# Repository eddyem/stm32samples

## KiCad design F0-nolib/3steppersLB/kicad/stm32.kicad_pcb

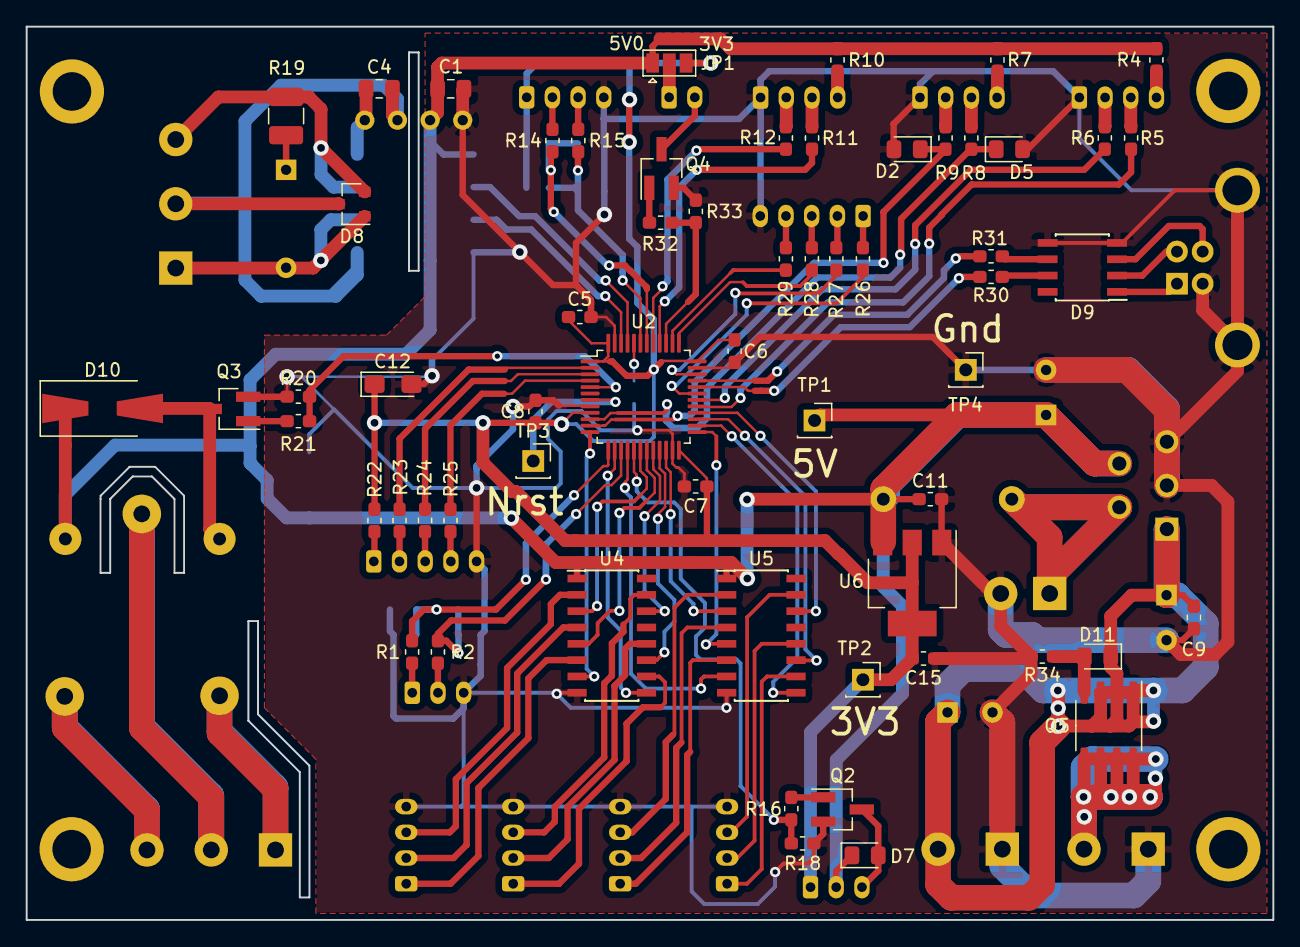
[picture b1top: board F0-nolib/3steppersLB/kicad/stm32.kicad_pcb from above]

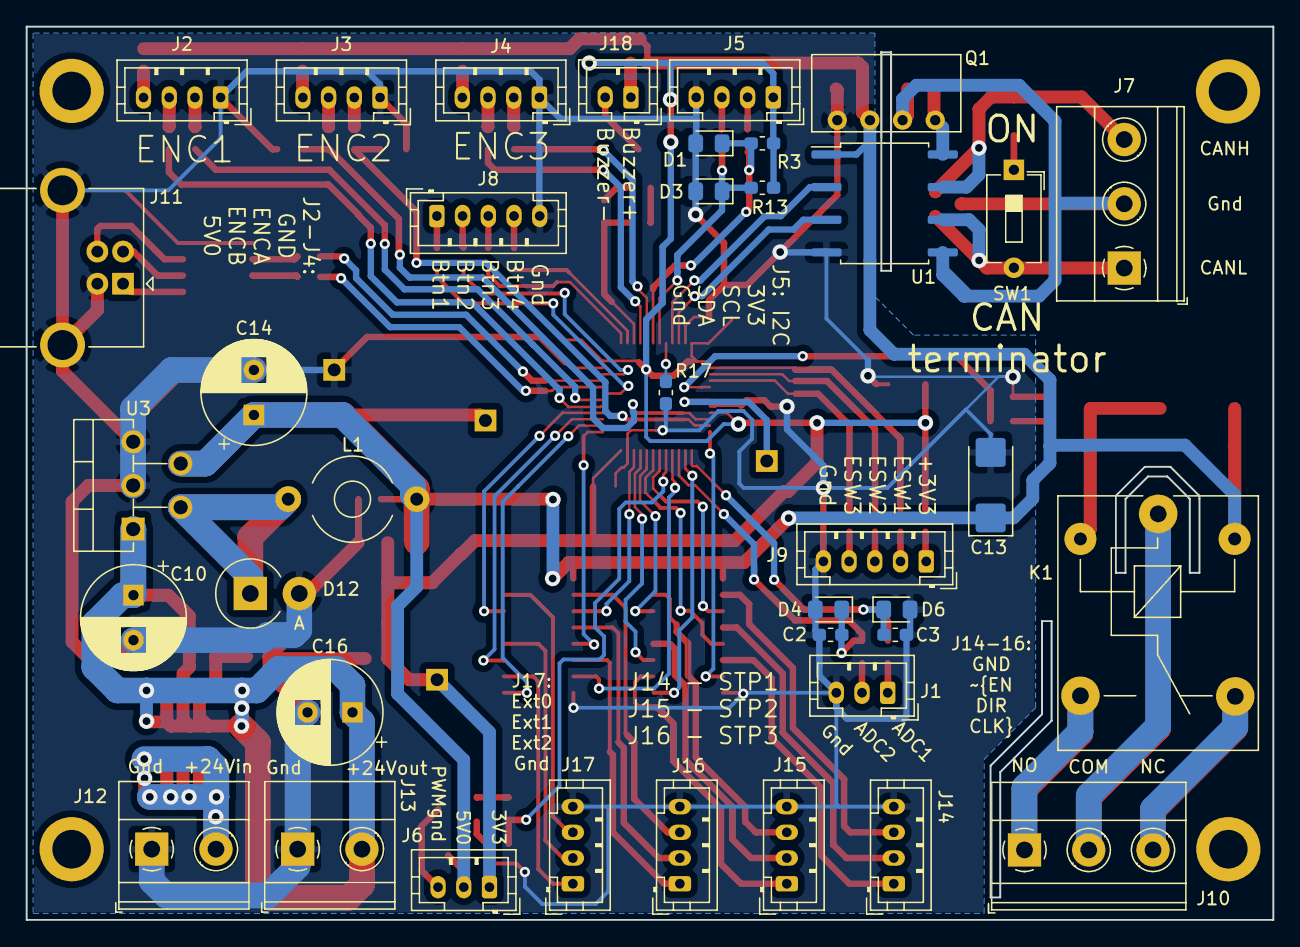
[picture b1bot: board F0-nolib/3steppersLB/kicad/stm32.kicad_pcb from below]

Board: 2 copper layers, 97.0 x 69.5 mm, 103 parts (38 on the bottom side), 98 nets.

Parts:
C1, C4: 1; C_0805_2012Metric_Pad1.15x1.40mm_HandSolder
C2, C3, C5, C6, C7, C8, C9, C11, C15: 0.1; C_0603_1608Metric_Pad1.05x0.95mm_HandSolder
C10, C14: 100u 16V; CP_Radial_D8.0mm_P3.50mm
C12: 47u 6V; CP_EIA-3216-18_Kemet-A_Pad1.58x1.35mm_HandSolder
C13: 47u 10V; CP_EIA-6032-28_Kemet-C_Pad2.25x2.35mm_HandSolder
C16: 100u 35V; CP_Radial_D8.0mm_P3.50mm
D1, D2, D3, D4, D5, D6: CESD3V3; D_0805_2012Metric_Pad1.15x1.40mm_HandSolder
D7: D; D_0805_2012Metric_Pad1.15x1.40mm_HandSolder
D8: PESD1CAN; SOT-23
D9: USB6B1; SOIC-8_3.9x4.9mm_P1.27mm
D10: SS14; D_SMA-SMB_Universal_Handsoldering
D11: MM3Z7V5; D_0805_2012Metric_Pad1.15x1.40mm_HandSolder
D12: 1N5822; D_DO-201_P3.81mm_Vertical_AnodeUp
J1, J6: 01x03; JST_PH_B3B-PH-K_1x03_P2.00mm_Vertical
J2, J3, J4, J5, J14, J15, J16, J17: Conn_01x04_Female; JST_PH_B4B-PH-K_1x04_P2.00mm_Vertical
J7, J10: Screw_Terminal_01x03; TerminalBlock_Phoenix_MKDS-1,5-3_1x03_P5.00mm_Horizontal
J8, J9: 01x05; JST_PH_B5B-PH-K_1x05_P2.00mm_Vertical
J11: USB_B; USB_B_OST_USB-B1HSxx_Horizontal
J12, J13: Screw_Terminal_01x02; TerminalBlock_Phoenix_MKDS-1,5-2_1x02_P5.00mm_Horizontal
J18: buzzer; JST_PH_B2B-PH-K_1x02_P2.00mm_Vertical
JP1: SolderJumper_3_Open; SolderJumper-3_P1.3mm_Open_Pad1.0x1.5mm
K1: G5LE-1; Relay_SPDT_SANYOU_SRD_Series_Form_C
L1: 100u; L_Toroid_Horizontal_D6.5mm_P10.00mm_Diameter7-5mm_Amidon-T25
P1, P2, P6, P7: Hole; Hole_3mm
Q1: B0505S; B0x0xS
Q2, Q3, Q4: SI2300; SOT-23_Handsoldering
Q5: IRF9310; SO-8_3.9x4.9mm_P1.27mm
R1, R2, R17, R18, R20, R33: 10k; R_0603_1608Metric_Pad1.05x0.95mm_HandSolder
R3, R13, R34: 4k7; R_0603_1608Metric_Pad1.05x0.95mm_HandSolder
R4, R7, R10, R30, R31: 22; R_0603_1608Metric_Pad1.05x0.95mm_HandSolder
R5, R6, R8, R9, R11, R12, R14, R15, R23, R24, R25, R26, R27, R28, R29: 100; R_0603_1608Metric_Pad1.05x0.95mm_HandSolder
R16, R21, R32: 330; R_0603_1608Metric_Pad1.05x0.95mm_HandSolder
R19: 120; R_1210_3225Metric_Pad1.42x2.65mm_HandSolder
R22: 47; R_0603_1608Metric_Pad1.05x0.95mm_HandSolder
SW1: SW_DIP_x01; SW_DIP_SPSTx01_Slide_6.7x4.1mm_W7.62mm_P2.54mm_LowProfile
TP1: 5V; PinSocket_1x01_P2.54mm_Vertical
TP2: 3.3V; PinSocket_1x01_P2.54mm_Vertical
TP3: NRST; PinSocket_1x01_P2.54mm_Vertical
TP4: Gnd; PinSocket_1x01_P2.54mm_Vertical
U1: ISO1050DUB; SOP-8_6.62x9.15mm_P2.54mm
U2: STM32F072C8Tx; LQFP-48_7x7mm_P0.5mm
U3: LM2576-5.0; TO-220-5_P3.4x3.7mm_StaggerEven_Lead3.8mm_Vertical
U4, U5: CD4050; SOIC-16_3.9x9.9mm_P1.27mm
U6: LM1117-3.3; SOT-223-3_TabPin2

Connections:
+3V3: C5.2, C6.2, C7.2, C8.2, C12.1, C15.1, J5.1, J6.1, JP1.3, R3.2, R13.2, R22.2, TP2.1, U2.1, U2.9, U2.24, U2.36, U2.48, U6.2
+5V: C1.1, C11.1, C13.1, C14.1, D7.1, D10.1, J6.2, JP1.1, K1.5, L1.1, Q1.2, R4.1, R7.1, R10.1, TP1.1, U1.1, U3.4, U4.1, U5.1, U6.3
/ADC1: C3.1, D6.1, R1.2, U2.13
/ADC2: C2.1, D4.1, R2.2, U2.15
/BTN1: R26.1, U2.31
/BTN2: R27.1, U2.34
/BTN3: R28.1, U2.37
/BTN4: R29.1, U2.38
/Buzzer: R32.2, R33.1, U2.39
/CANH: D8.2, J7.3, R19.2, U1.7
/CANL: D8.1, J7.1, SW1.2, U1.6
/CAN_Rx: U1.2, U2.45
/CAN_Tx: U1.3, U2.46
/CLK1: U2.12, U4.7
/CLK2: U2.14, U4.9
/CLK3: U2.16, U5.7
/DIR1: U2.19, U4.5
/DIR2: U2.21, U4.11
/DIR3: U2.25, U5.5
/ESW1: R23.2, U2.2
/ESW2: R24.2, U2.3
/ESW3: R25.2, U2.4
/Enc1a: R5.1, U2.29
/Enc1b: R6.1, U2.30
/Enc2a: D5.1, R8.1, U2.10
/Enc2b: D2.1, R9.1, U2.11
/Enc3a: R11.1, U2.40
/Enc3b: R12.1, U2.41
/Ext0: U2.26, U5.9
/Ext1: U2.27, U5.11
/Ext2: U2.28, U5.14
/G1: D7.2, J6.3, Q2.3
/I2C1_SCL: D1.1, R3.1, R14.2, U2.42
/I2C1_SDA: D3.1, R13.1, R15.2, U2.43
/PWM: R16.2, R18.1, U2.17
/Relay: R20.2, R21.2, U2.5
/~EN1: U2.18, U4.3
/~EN2: U2.20, U4.14
/~EN3: U2.22, U5.3
Earth: C4.2, D8.3, J7.2, Q1.3, U1.5
GND: C1.2, C2.2, C3.2, C5.1, C6.1, C7.1, C8.1, C9.2, C10.2, C11.2, C12.2, C13.2, C14.2, C15.2, C16.2, D1.2, D2.2, D3.2, D4.2, D5.2, D6.2, D9.4, D9.5, D12.2, J1.3, J2.1, J3.1, J4.1, J5.4, J8.5, J9.5, J11.4, J11.5, J12.1, J13.1, J14.4, J15.4, J16.4, J17.4, Q1.1, Q2.2, Q3.2, Q4.2, R17.2, R18.2, R20.1, R33.2, R34.2, TP4.1, U1.4, U2.8, U2.23, U2.35, U2.47, U3.3, U3.5, U4.8, U5.8, U6.1
unnamed: C4.1, Q1.4, U1.8
unnamed: C9.1, C10.1, C16.1, D11.1, J13.2, Q5.1, Q5.2, Q5.3, U3.1
unnamed: D9.1, J11.1
unnamed: D9.2, J11.2
unnamed: D9.3, J11.3
unnamed: D9.6, R31.1
unnamed: D9.7, R30.1
unnamed: D10.2, K1.2, Q3.3
unnamed: D11.2, Q5.4, R34.1
unnamed: D12.1, L1.2, U3.2
unnamed: J1.1, R1.1
unnamed: J1.2, R2.1
unnamed: J2.2, R6.2
unnamed: J2.3, R5.2
unnamed: J2.4, R4.2
unnamed: J3.2, R9.2
unnamed: J3.3, R8.2
unnamed: J3.4, R7.2
unnamed: J4.2, R12.2
unnamed: J4.3, R11.2
unnamed: J4.4, R10.2
unnamed: J5.2, R14.1
unnamed: J5.3, R15.1
unnamed: J8.1, R26.2
unnamed: J8.2, R27.2
unnamed: J8.3, R28.2
unnamed: J8.4, R29.2
unnamed: J9.1, R22.1
unnamed: J9.2, R23.1
unnamed: J9.3, R24.1
unnamed: J9.4, R25.1
unnamed: J10.1, K1.3
unnamed: J10.2, K1.1
unnamed: J10.3, K1.4
unnamed: J12.2, Q5.5, Q5.6, Q5.7, Q5.8
unnamed: J14.1, U4.6
unnamed: J14.2, U4.4
unnamed: J14.3, U4.2
unnamed: J15.1, U4.10
unnamed: J15.2, U4.12
unnamed: J15.3, U4.15
unnamed: J16.1, U5.6
unnamed: J16.2, U5.4
unnamed: J16.3, U5.2
unnamed: J17.1, U5.10
unnamed: J17.2, U5.12
unnamed: J17.3, U5.15
unnamed: J18.1, JP1.2
unnamed: J18.2, Q4.3
unnamed: Q2.1, R16.1
unnamed: Q3.1, R21.1
unnamed: Q4.1, R32.1
unnamed: R17.1, U2.44
unnamed: R19.1, SW1.1
unnamed: R30.2, U2.32
unnamed: R31.2, U2.33
unnamed: TP3.1, U2.7

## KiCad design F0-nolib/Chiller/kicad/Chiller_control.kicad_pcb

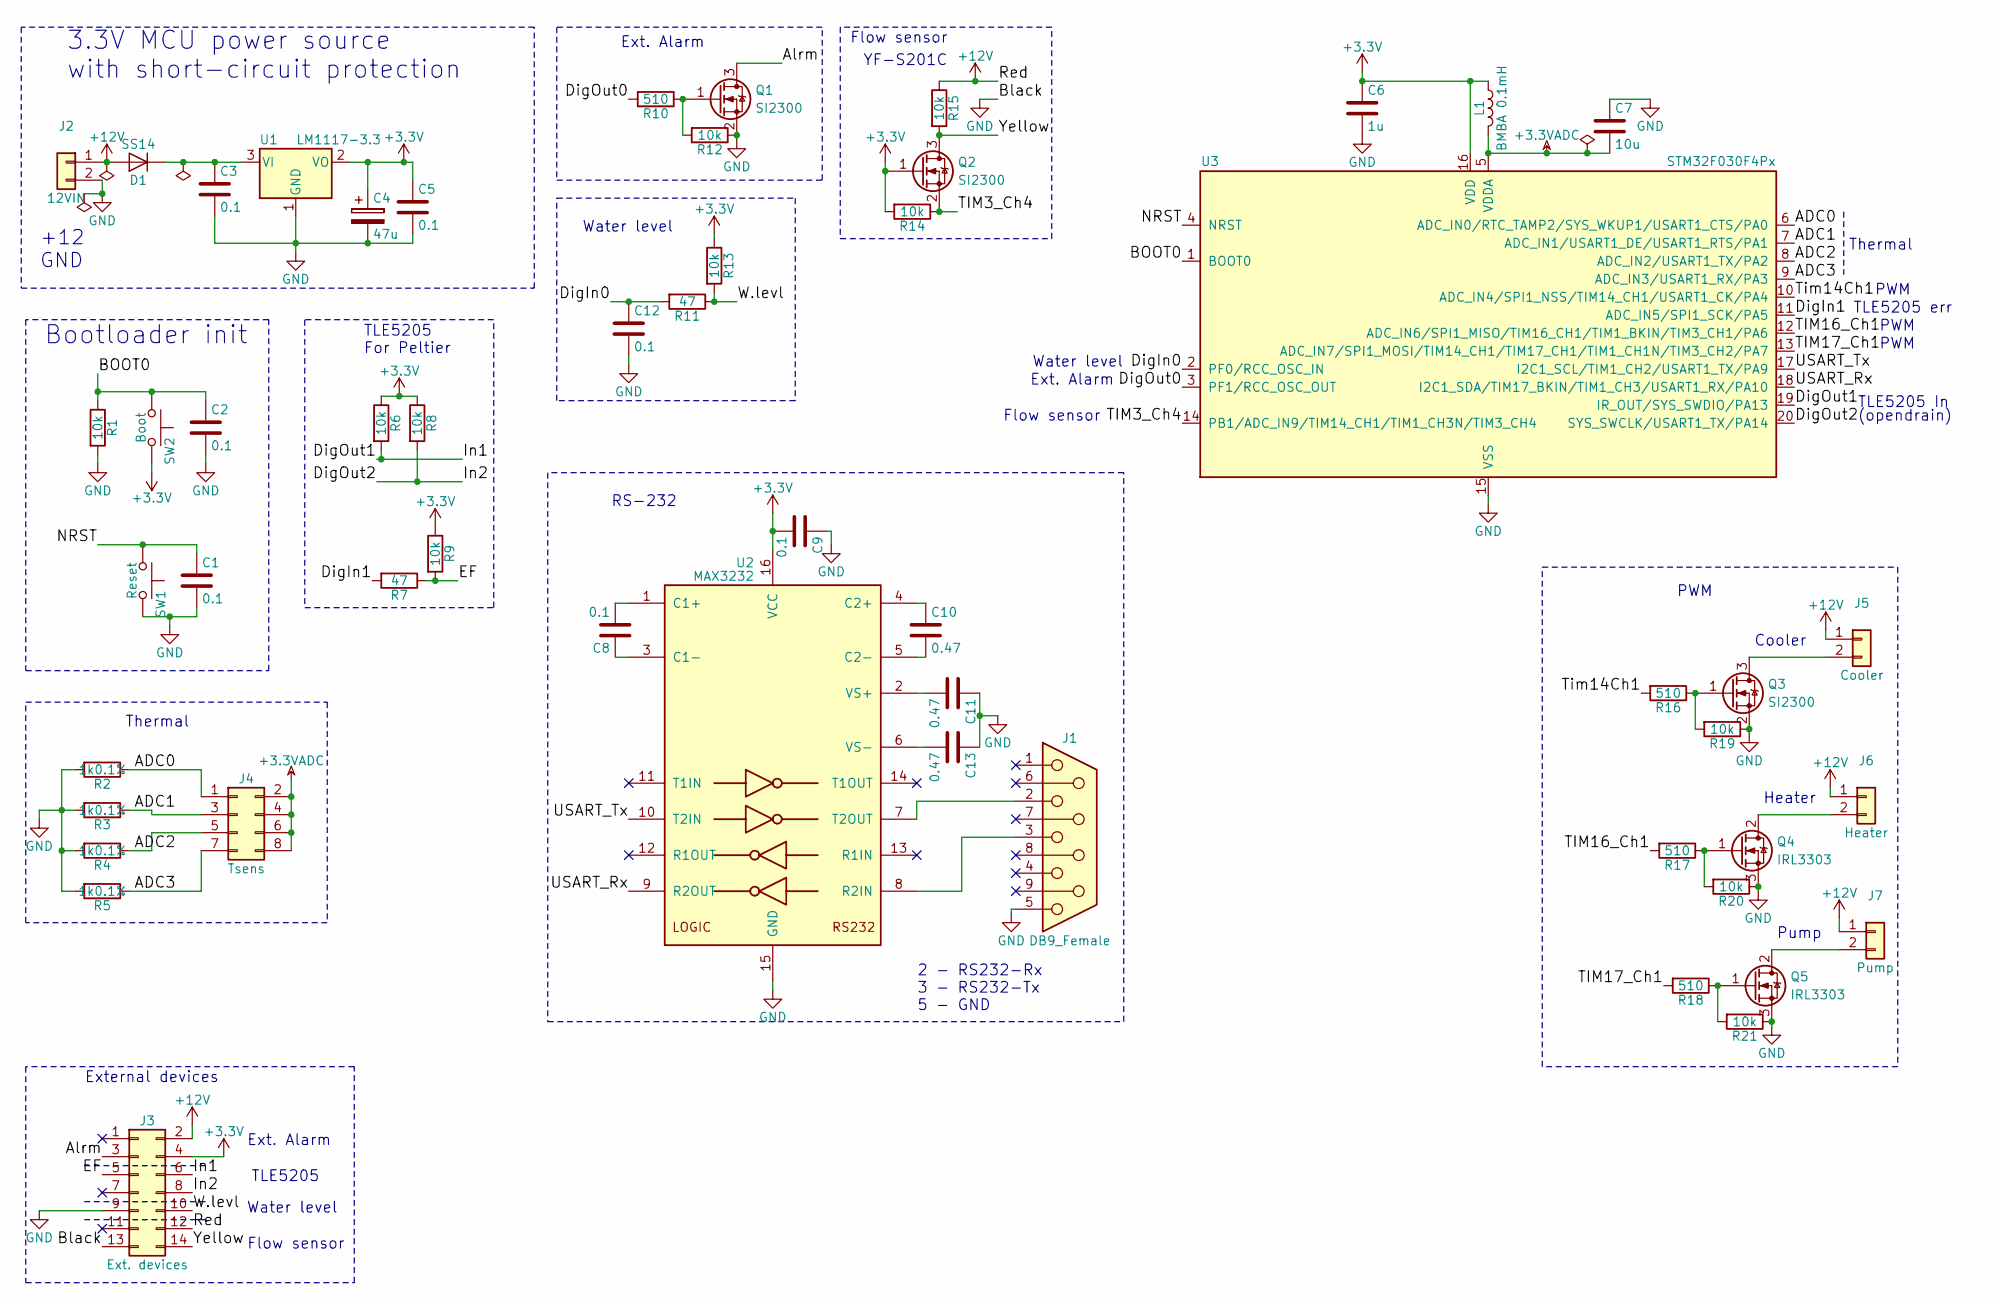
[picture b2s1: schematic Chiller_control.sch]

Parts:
C1, C2, C3, C5, C8, C9, C12: 0.1; C_0603_HandSoldering
C4: 47u; CP_Tantalum_Case-A_EIA-3216-18_Hand
C6: 1u; C_0805_HandSoldering
C7: 10u; C_1206_HandSoldering
C10, C11, C13: 0.47; C_0805_HandSoldering
D1: SS14; D_SMA_Handsoldering
J1: DB9_Female; DB9-F
J2: 12VIN; TerminalBlock_Pheonix_MKDS1.5-2pol
J3: Ext. devices; PinSocket_2x07_P2.54mm_Vertical
J4: Tsens; PinSocket_2x04_P2.54mm_Vertical
J5: Cooler; TerminalBlock_Pheonix_MKDS1.5-2pol
J6: Heater; TerminalBlock_Pheonix_MKDS1.5-2pol
J7: Pump; TerminalBlock_Pheonix_MKDS1.5-2pol
L1: BMBA 0.1mH; R_0805_HandSoldering
Q1, Q2, Q3: SI2300; SOT-23_Handsoldering
Q4, Q5: IRL3303; TO-220_Horizontal
R1, R6, R8, R9, R12, R13, R14, R15, R19, R20, R21: 10k; R_0603_HandSoldering
R2, R3, R4, R5: 1k0.1%; R_0805_HandSoldering
R7, R11: 47; R_0805_HandSoldering
R10, R16, R17, R18: 510; R_0603_HandSoldering
SW1: Reset; SW_SPST_FSMSM
SW2: Boot; SW_SPST_FSMSM
U1: LM1117-3.3; SOT-223
U2: MAX3232; SOIC-16_3.9x9.9mm_Pitch1.27mm
U3: STM32F030F4Px; TSSOP-20_4.4x6.5mm_Pitch0.65mm

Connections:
+3.3VADC: C7.2, J4.2, J4.4, J4.6, J4.8, L1.2, U3.5 (VDDA)
+3V3: C4.1, C5.1, C6.1, C9.2, J3.4, L1.1, Q2.1 (G), R6.1, R8.1, R9.1, R13.1, R14.2, SW2.2, U1.2 (VO), U2.16 (VCC), U3.16 (VDD)
+12V: D1.2 (A), J2.1, J3.2, J3.12, J5.1, J6.1, J7.1, R15.1
/ADC0: J4.1, R2.1, U3.6 (ADC_IN0/RTC_TAMP2/SYS_WKUP1/USART1_CTS/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)
/ADC1: J4.3, R3.1, U3.7 (ADC_IN1/USART1_DE/USART1_RTS/PA1)
/ADC2: J4.5, R4.1, U3.8 (ADC_IN2/USART1_TX/PA2)
/ADC3: J4.7, R5.1, U3.9 (ADC_IN3/USART1_RX/PA3)
/Alrm: J3.3, Q1.3 (D)
/BOOT0: C2.1, R1.1, SW2.1, U3.1 (BOOT0)
/DigIn0: C12.1, R11.2, U3.2 (PF0/RCC_OSC_IN)
/DigIn1: R7.2, U3.11 (ADC_IN5/SPI1_SCK/PA5)
/DigOut0: R10.2, U3.3 (PF1/RCC_OSC_OUT)
/DigOut1: J3.6, R6.2, U3.19 (IR_OUT/SYS_SWDIO/PA13)
/DigOut2: J3.8, R8.2, U3.20 (SYS_SWCLK/USART1_TX/PA14)
/EF: J3.5, R7.1, R9.2
/NRST: C1.1, SW1.1, U3.4 (NRST)
/TIM3_Ch4: Q2.2 (S), R14.1, U3.14 (PB1/ADC_IN9/TIM14_CH1/TIM1_CH3N/TIM3_CH4)
/TIM16_Ch1: R17.2, U3.12 (ADC_IN6/SPI1_MISO/TIM16_CH1/TIM1_BKIN/T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)
/TIM17_Ch1: R18.2, U3.13 (ADC_IN7/SPI1_MOSI/TIM14_CH1/TIM17_CH1/T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)
/Tim14Ch1: R16.2, U3.10 (ADC_IN4/SPI1_NSS/TIM14_CH1/USART1_CK/PA4)
/USART_Rx: U2.9 (R2OUT), U3.18 (I2C1_SDA/TIM17_BKIN/TIM1_CH3/USART1_RX/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)
/USART_Tx: U2.10 (T2IN), U3.17 (I2C1_SCL/TIM1_CH2/USART1_TX/PA9)
/W.levl: J3.10, R11.1, R13.2
/Yellow: J3.14, Q2.3 (D), R15.2
GND: C1.2, C2.2, C3.2, C4.2, C5.2, C6.2, C7.1, C9.1, C11.1, C12.2, C13.1, J1.5, J2.2, J3.9, J3.13, Q1.2 (S), Q3.2 (S), Q4.3 (S), Q5.3 (S), R1.2, R2.2, R3.2, R4.2, R5.2, R12.1, R19.1, R20.1, R21.1, SW1.2, U1.1 (GND), U2.15 (GND), U3.15 (VSS)
unnamed: C3.1, D1.1 (K), U1.3 (VI)
unnamed: C8.1, U2.3 (C1-)
unnamed: C8.2, U2.1 (C1+)
unnamed: C10.1, U2.4 (C2+)
unnamed: C10.2, U2.5 (C2-)
unnamed: C11.2, U2.2 (VS+)
unnamed: C13.2, U2.6 (VS-)
unnamed: J1.2, U2.7 (T2OUT)
unnamed: J1.3, U2.8 (R2IN)
unnamed: J5.2, Q3.3 (D)
unnamed: J6.2, Q4.2 (D)
unnamed: J7.2, Q5.2 (D)
unnamed: Q1.1 (G), R10.1, R12.2
unnamed: Q3.1 (G), R16.1, R19.2
unnamed: Q4.1 (G), R17.1, R20.2
unnamed: Q5.1 (G), R18.1, R21.2

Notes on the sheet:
3.3V MCU power source with short-circuit protection
Bootloader init
+12 GND
PWM
Flow sensor
Thermal
TLE5205 err
Water level
Ext. Alarm
TLE5205 In
(opendrain)
TLE5205 For Peltier
YF-S201C
Cooler
Heater
Pump
2 - RS232-Rx 3 - RS232-Tx 5 - GND
RS-232
TLE5205
External devices

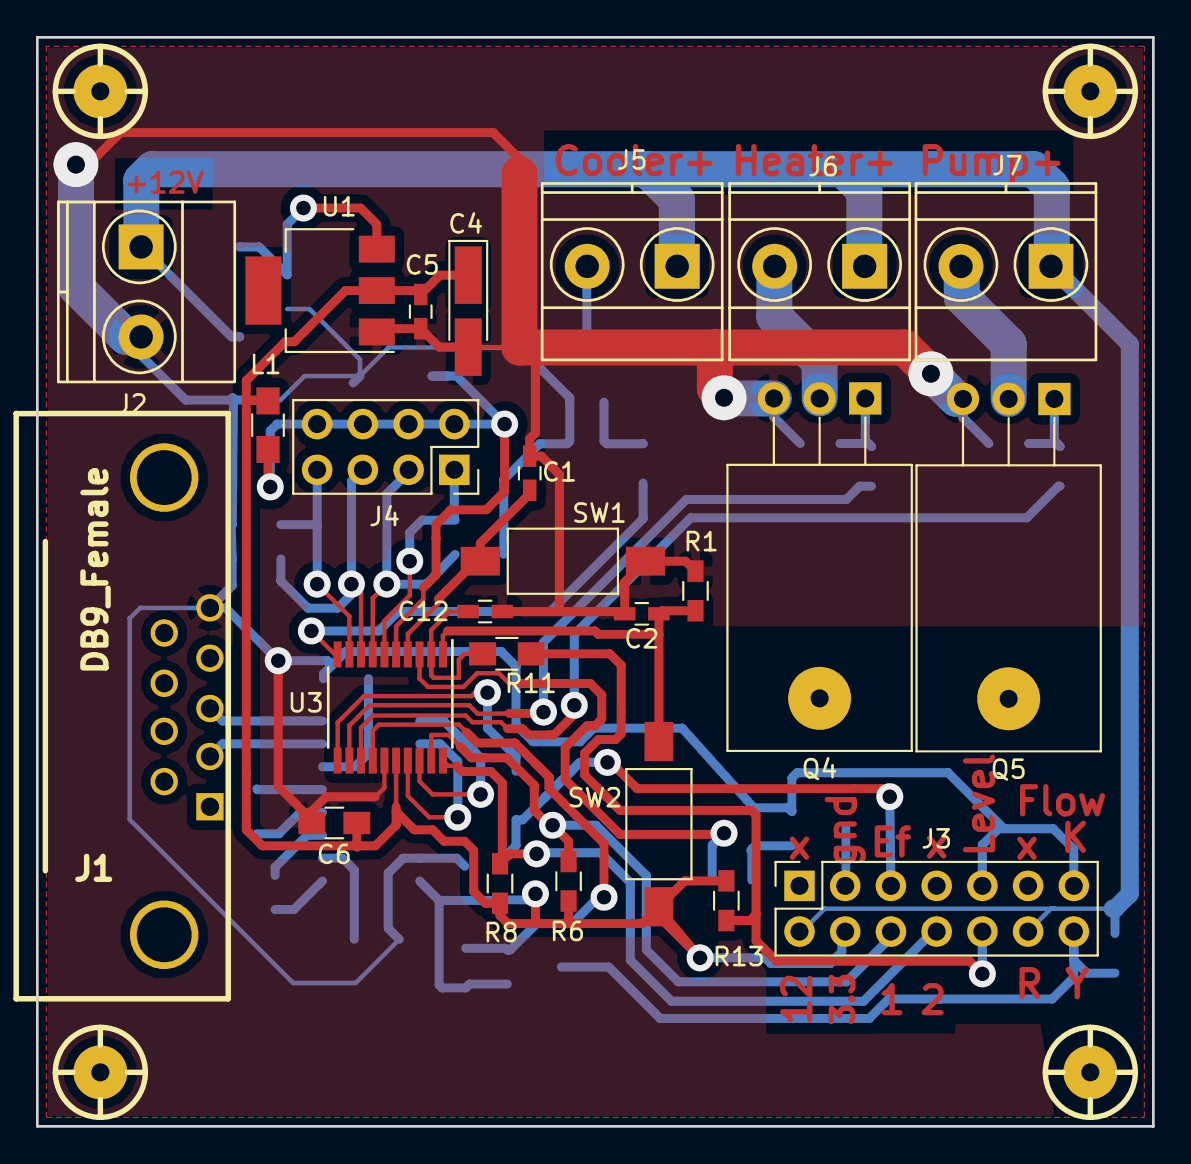
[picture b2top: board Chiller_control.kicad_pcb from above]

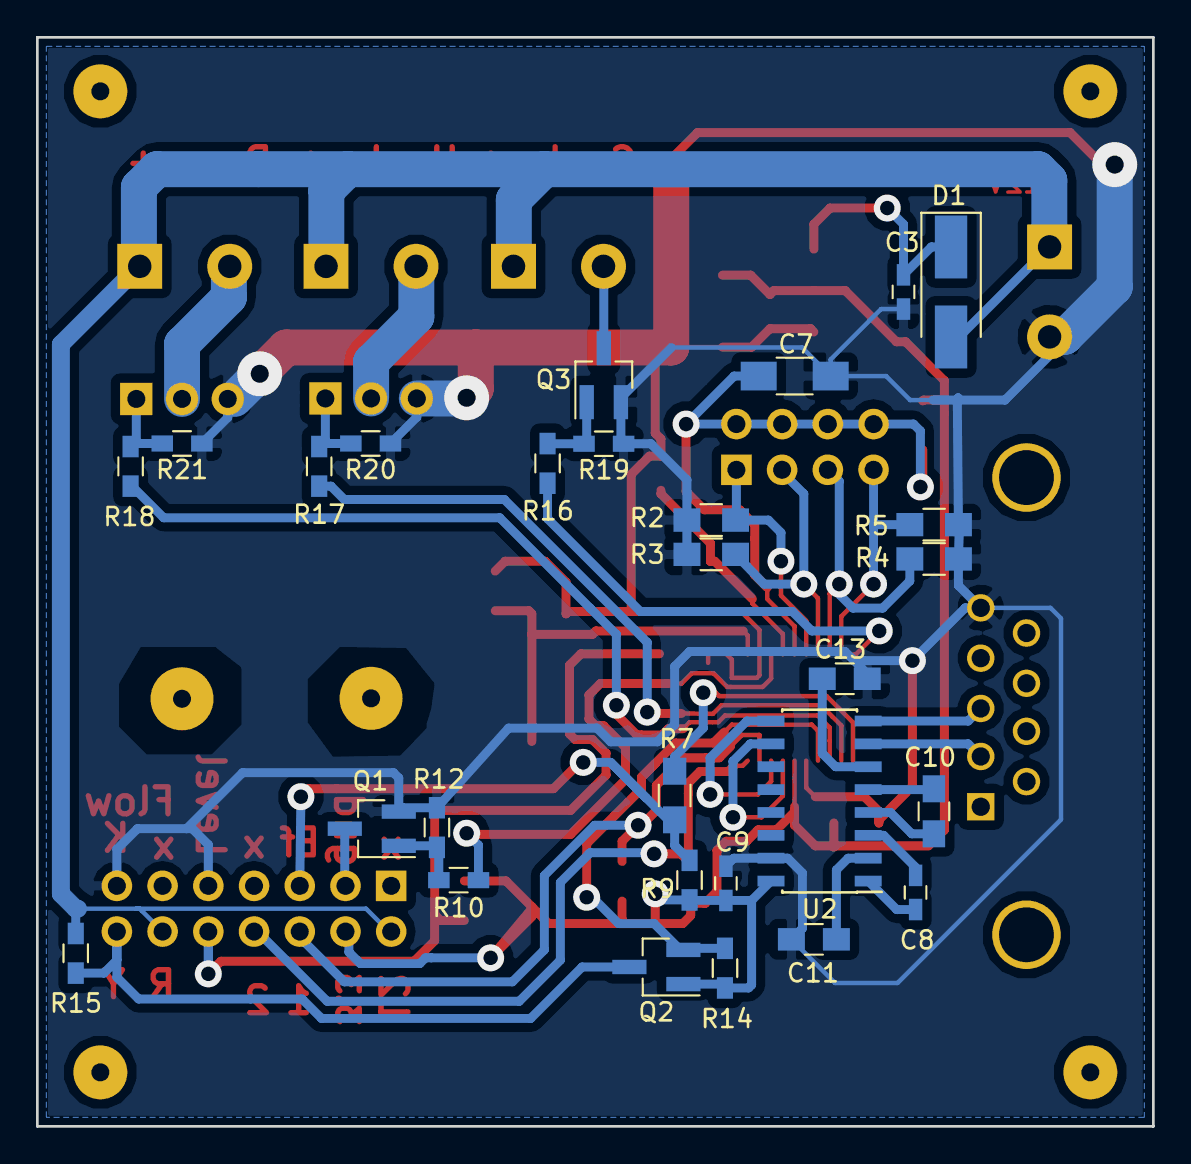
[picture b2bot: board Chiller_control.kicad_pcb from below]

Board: 2 copper layers, 62.0 x 60.5 mm, 57 parts (28 on the bottom side), 41 nets.

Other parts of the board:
hole_3mm, hole_3mm#2, hole_3mm#3, hole_3mm#4: Val**; hole_3mm

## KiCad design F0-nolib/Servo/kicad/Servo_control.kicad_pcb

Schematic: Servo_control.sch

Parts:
BZ1: Buzzer; Buzzer_12x9.5RM7.6
C1, C2, C3, C5, C6, C8, C10, C11, C12: 0.1; C_0603_1608Metric_Pad0.84x1.00mm_HandSolder
C4: 47u; CP_EIA-3216-18_Kemet-A_Pad1.53x1.40mm_HandSolder
C7, C9: 22p; C_0603_1608Metric_Pad0.84x1.00mm_HandSolder
C13: 1u; C_0805_2012Metric_Pad1.15x1.50mm_HandSolder
C14: 10u; C_1206_3216Metric_Pad1.24x1.80mm_HandSolder
D1: USB6B1; SOIC-8_3.9x4.9mm_P1.27mm
D2: SP0504BAHT; SOT-23-5
D3, D4: SMAJ5.0; D_SMA_Handsoldering
D5: SS14; D_SMA_Handsoldering
J1: USB_B_Micro; USB_Micro-B_Wuerth-629105150521
J2: ADC_in; PinHeader_1x06_P2.54mm_Vertical
J3: Jumper0; PinHeader_1x02_P2.54mm_Vertical
J4: Jumper1; PinHeader_1x02_P2.54mm_Vertical
J5: Dig_In; PinHeader_1x03_P2.54mm_Vertical
J6: Ext_LED; PinHeader_1x02_P2.54mm_Vertical
J7: Servo1; PinHeader_1x03_P2.54mm_Vertical
J8: Servo2; PinHeader_1x03_P2.54mm_Vertical
J9: Servo3; PinHeader_1x03_P2.54mm_Vertical
J10: 5V; PinHeader_1x02_P2.54mm_Vertical
L1: BMBA 0.1mH; L_0805_2012Metric_Pad1.15x1.50mm_HandSolder
Q1, Q3, Q4, Q5: 2N7002; SOT-23
Q2: SI2300; SOT-23
R1, R7, R9, R15, R16, R17: 10k; R_0805_2012Metric_Pad1.15x1.50mm_HandSolder
R2, R3, R4, R5: 220; R_0805_2012Metric_Pad1.15x1.50mm_HandSolder
R6, R8, R12, R13, R14: 510; R_0805_2012Metric_Pad1.15x1.50mm_HandSolder
R10, R11: 1k; R_0805_2012Metric_Pad1.15x1.50mm_HandSolder
SW1: Reset; SW_SPST_FSMSM
SW2: Boot; SW_SPST_FSMSM
U1: LM1117-3.3; SOT-223-3_TabPin2
U2: CH340G; SOIC-16_3.9x9.9mm_P1.27mm
U3: STM32F030F4Px; TSSOP-20_4.4x6.5mm_P0.65mm
Y1: 12MHz; Crystal_HC49-U_Vertical

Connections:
+3.3VADC: C14.2, J2.6, L1.2, U3.5 (VDDA)
+3V3: C4.1, C5.1, C13.1, L1.1, SW2.2, U1.2 (VO), U2.16, U3.16 (VDD)
+5V: BZ1.1, C1.1, D5.1, J6.1, J7.2, J8.2, J9.2, J10.1, U1.3 (VI)
/ADC0: C12.1, D2.3, R2.1, U3.6 (ADC_IN0/RTC_TAMP2/SYS_WKUP1/USART1_CTS/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)
/ADC1: C11.1, D2.1, R3.1, U3.7 (ADC_IN1/USART1_DE/USART1_RTS/PA1)
/ADC2: C10.1, D2.5, R4.1, U3.8 (ADC_IN2/USART1_TX/PA2)
/ADC3: C8.1, D2.4, R5.1, U3.9 (ADC_IN3/USART1_RX/PA3)
/BOOT0: C3.1, R1.2, SW2.1, U3.1 (BOOT0)
/DigIn0: D3.1, R11.1, U3.19 (IR_OUT/SYS_SWDIO/PA13)
/DigIn1: D4.1, R10.1, U3.20 (SYS_SWCLK/USART1_TX/PA14)
/DigOut0: R6.2, R7.2, U3.2 (PF0/RCC_OSC_IN)
/DigOut1: R8.2, R9.2, U3.3 (PF1/RCC_OSC_OUT)
/Jumper0: J3.2, U3.10 (ADC_IN4/SPI1_NSS/TIM14_CH1/USART1_CK/PA4)
/Jumper1: J4.2, U3.11 (ADC_IN5/SPI1_SCK/PA5)
/NRST: C2.1, SW1.1, U3.4 (NRST)
/TIM3_CH1: R12.2, R15.2, U3.12 (ADC_IN6/SPI1_MISO/TIM16_CH1/TIM1_BKIN/T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)
/TIM3_CH2: R13.2, R16.2, U3.13 (ADC_IN7/SPI1_MOSI/TIM14_CH1/TIM17_CH1/T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)
/TIM3_CH4: R14.2, R17.2, U3.14 (PB1/ADC_IN9/TIM14_CH1/TIM1_CH3N/TIM3_CH4)
/USART_Rx: U2.2, U3.18 (I2C1_SDA/TIM17_BKIN/TIM1_CH3/USART1_RX/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)
/USART_Tx: U2.3, U3.17 (I2C1_SCL/TIM1_CH2/USART1_TX/PA9)
GND: C1.2, C2.2, C3.2, C4.2, C5.2, C6.2, C7.2, C8.2, C9.2, C10.2, C11.2, C12.2, C13.2, C14.1, D1.5, D2.2, D3.2, D4.2, J2.1, J3.1, J4.1, J5.1, J7.1, J8.1, J9.1, J10.2, Q1.2 (S), Q2.2 (S), Q3.2 (S), Q4.2 (S), Q5.2 (S), R1.1, R7.1, R9.1, R15.1, R16.1, R17.1, SW1.2, U1.1 (GND), U2.1, U3.15 (VSS)
unnamed: BZ1.2, Q1.3 (D)
unnamed: C6.1, U2.4
unnamed: C7.1, U2.7, Y1.1
unnamed: C9.1, U2.8, Y1.2
unnamed: D1.1, J1.1 (VBUS)
unnamed: D1.2, J1.2 (D-)
unnamed: D1.3, J1.3 (D+)
unnamed: D1.4, J1.5 (GND), J1.6 (Shield)
unnamed: D1.6, U2.6
unnamed: D1.7, U2.5
unnamed: D1.8, D5.2
unnamed: J2.2, R5.2
unnamed: J2.3, R4.2
unnamed: J2.4, R3.2
unnamed: J2.5, R2.2
unnamed: J5.2, R11.2
unnamed: J5.3, R10.2
unnamed: J6.2, Q2.3 (D)
unnamed: J7.3, Q3.3 (D)
unnamed: J8.3, Q4.3 (D)
unnamed: J9.3, Q5.3 (D)
unnamed: Q1.1 (G), R6.1
unnamed: Q2.1 (G), R8.1
unnamed: Q3.1 (G), R12.1
unnamed: Q4.1 (G), R13.1
unnamed: Q5.1 (G), R14.1

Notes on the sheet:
MCU power source
Bootloader init
PWM
Alarm
Alarm Buzzer
ADC
USB
Ext. load

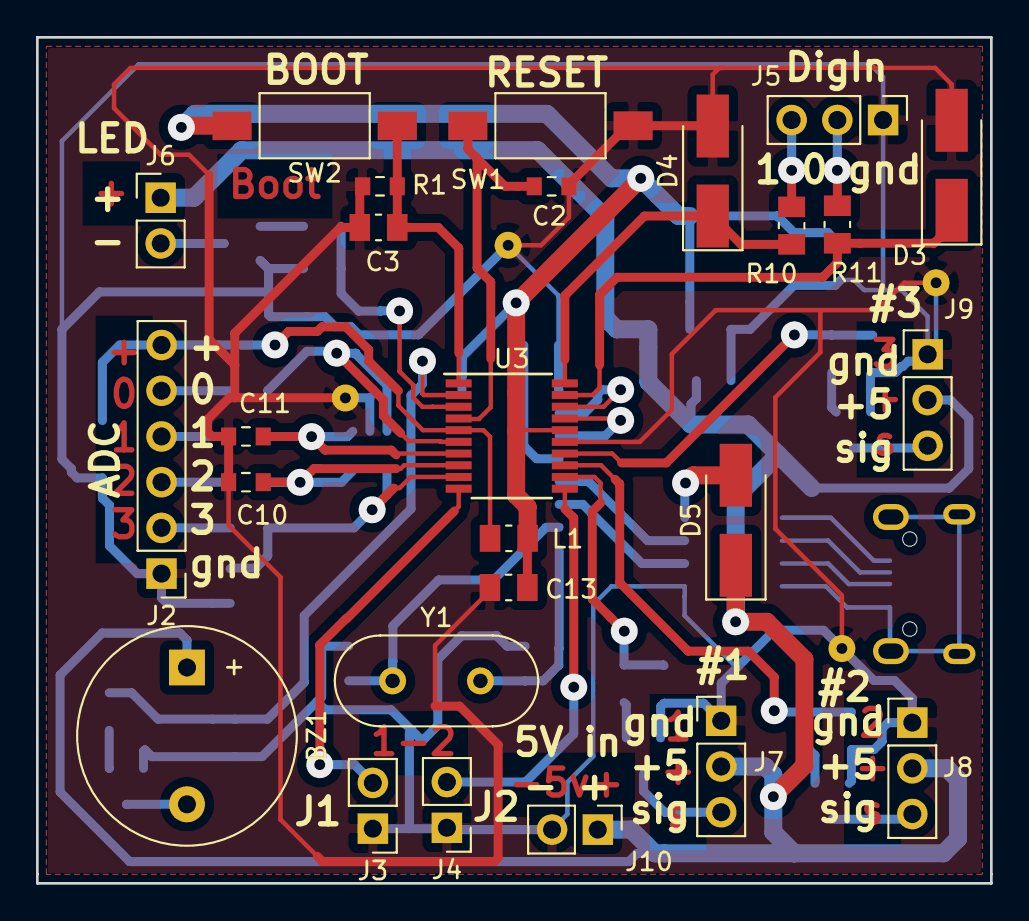
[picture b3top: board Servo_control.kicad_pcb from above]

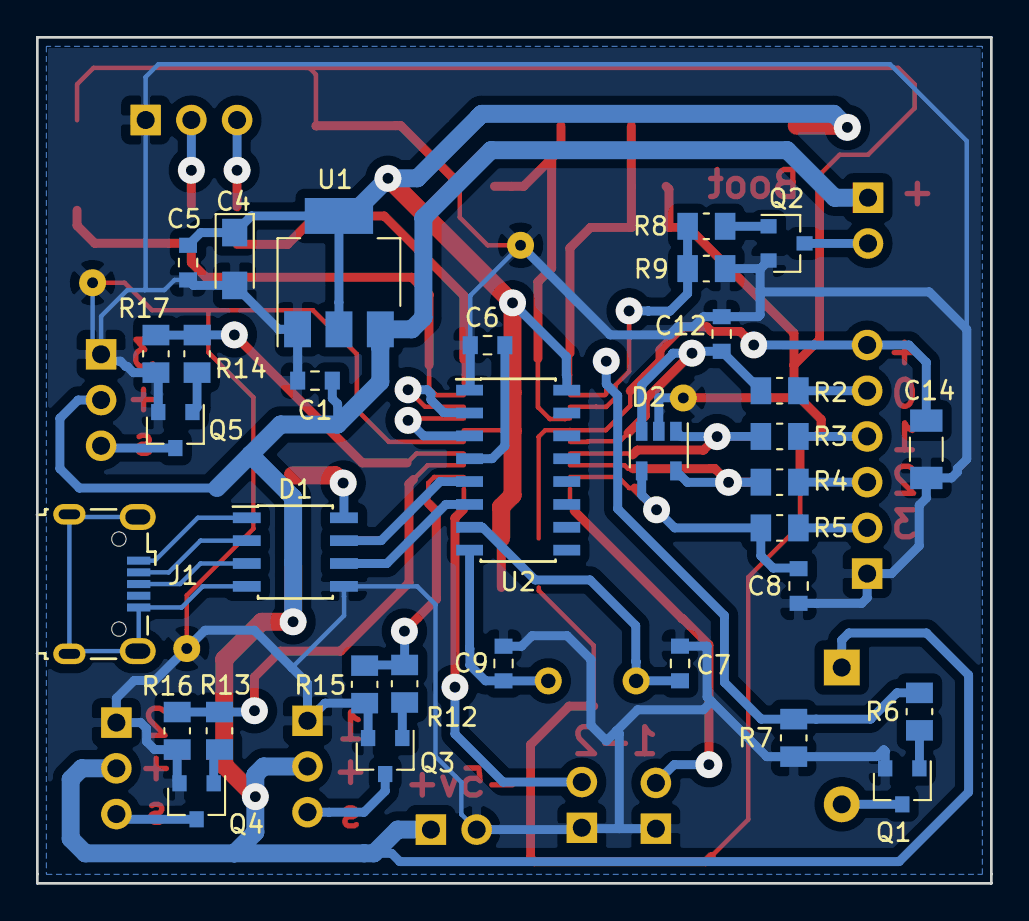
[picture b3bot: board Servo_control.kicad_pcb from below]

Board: 2 copper layers, 53.0 x 47.0 mm, 59 parts (33 on the bottom side), 47 nets.

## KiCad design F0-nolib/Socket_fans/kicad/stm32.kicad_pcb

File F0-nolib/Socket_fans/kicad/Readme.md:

# FAN controller for electronics box

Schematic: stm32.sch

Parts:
C1, C2, C3, C4, C5, C6, C8, C13, C14, C15, C16, C17, C18, C19, C20: 0.1; C_0603_1608Metric_Pad1.05x0.95mm_HandSolder
C7: 47uF, 10V; CP_EIA-6032-28_Kemet-C_Pad2.25x2.35mm_HandSolder
C9: 10uF, 10V; C_1206_3216Metric_Pad1.42x1.75mm_HandSolder
C10: 47u; CP_Radial_D8.0mm_P3.50mm
D1, D2, D4, D5, D6, D9: 1N5819; D_SOD-323_HandSoldering
D3: MM3Z7V5; D_0805_2012Metric_Pad1.15x1.40mm_HandSolder
D7: MM3Z4V3; D_0805_2012Metric_Pad1.15x1.40mm_HandSolder
J1: 12VIN; TerminalBlock_Phoenix_MKDS-1,5-2_1x02_P5.00mm_Horizontal
J2: thermal; PinSocket_2x04_P2.54mm_Vertical
J3: Buzzer; JST_EH_B2B-EH-A_1x02_P2.50mm_Vertical
J4: cooler3; JST_EH_B2B-EH-A_1x02_P2.50mm_Vertical
J5, J6: FAN; FanPinHeader_1x04_P2.54mm_Vertical
J7, J10: Conn_01x02_Female; PinSocket_1x02_P2.54mm_Vertical
J8: MKDS; TerminalBlock_Phoenix_MKDS-1,5-2_1x02_P5.00mm_Horizontal
K1: SRD-12VDC; Relay_SPDT_SANYOU_SRD_Series_Form_C
L1: BMBA 0.1mH; L_0805_2012Metric_Pad1.15x1.40mm_HandSolder
P1: USB_A; USB_B_OST_USB-B1HSxx_Horizontal
P2, P3, P4, P5: Hole; MountingHole_3.2mm_M3
Q1: AO3401; SOT-23_Handsoldering
Q2, Q3, Q4, Q5, Q6: IRLML2502; SOT-23_Handsoldering
R1, R2, R4, R6, R8, R13, R14, R16, R17, R34: 10k; R_0603_1608Metric_Pad1.05x0.95mm_HandSolder
R3, R5, R7, R9: 4k7, 1%; R_0805_2012Metric_Pad1.15x1.40mm_HandSolder
R10, R11, R12, R15, R18, R19, R20, R21, R24, R25, R32: 510; R_0603_1608Metric_Pad1.05x0.95mm_HandSolder
R22: 47k; R_0603_1608Metric_Pad1.05x0.95mm_HandSolder
R23, R30, R31: 22; R_0603_1608Metric_Pad1.05x0.95mm_HandSolder
R26: 3.3k; R_0603_1608Metric_Pad1.05x0.95mm_HandSolder
R27: 1k; R_0603_1608Metric_Pad1.05x0.95mm_HandSolder
R28, R29: 4.7k; R_0603_1608Metric_Pad1.05x0.95mm_HandSolder
SW1, SW2: SW_Push; PinSocket_1x02_P2.54mm_Vertical
U1: LM1117-3.3; SOT-223-3_TabPin2
U2: L7805; TO-220-3_Vertical
U3: STM32F072CBTx; LQFP-48_7x7mm_P0.5mm
U4: USBLC6-2SC6; SOT-23-6

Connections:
+3V3: C6.1, C7.1, C15.2, C17.2, C19.2, J2.2, J2.4, J2.6, J2.8, L1.1, R23.2, U1.2, U3.1, U3.24, U3.36, U3.48
+5V: D1.1, D2.1, R28.1, U1.3
+12V: C3.1, C10.1, D3.1, D4.1, D5.1, D6.1, D9.1, J3.2, J4.1, J5.2, J6.2, K1.2, Q1.2, R26.1, U2.1
/5Vin: C8.1, C9.1, D1.2, U2.3
/5Vusb: D2.2, P1.1, U4.5
/ADC0: C1.2, R2.2, U3.10
/ADC1: C2.2, R4.2, U3.11
/ADC2: C4.2, R6.2, U3.12
/ADC3: C5.2, R8.2, U3.13
/AIN0: C16.1, D7.1, R26.2, R27.1, U3.14
/AIN1: C18.1, R28.2, R29.1, U3.15
/BOOT0: J7.2, R22.1, U3.44
/Btn0: R24.1, U3.27
/Btn1: R25.1, U3.28
/Buzzer: R12.2, R16.2, U3.37
/Cooler0: R11.2, R14.2, U3.40
/Cooler1: R10.2, R13.2, U3.41
/NRST: J10.1, U3.7
/Relay: R32.2, R34.1, U3.2
/TIM1_CH1: R21.1, U3.29
/TIM1_CH2: R20.1, U3.30
/TIM1_CH3: R15.2, R17.2, U3.31
/TIM3_CH1: R19.1, U3.16
/TIM14_CH1: R18.1, U3.17
GND: C1.1, C2.1, C3.2, C4.1, C5.1, C6.2, C7.2, C8.2, C9.2, C10.2, C13.2, C14.2, C15.1, C16.2, C17.1, C18.2, C19.1, C20.2, D7.2, J1.2, J10.2, P1.4, P1.5, Q2.2 (S), Q3.2 (S), Q4.2 (S), Q5.2 (S), Q6.2 (S), R1.2, R3.1, R5.1, R7.1, R9.1, R13.1, R14.1, R16.1, R17.1, R22.2, R27.2, R29.2, R34.2, SW1.1, SW2.1, U1.1, U2.2, U3.8, U3.23, U3.35, U3.47, U4.2
unnamed: C13.1, R24.2, SW1.2
unnamed: C14.1, R25.2, SW2.2
unnamed: C20.1, L1.2, U3.9
unnamed: D3.2, Q1.1, R1.1
unnamed: D4.2, J5.1, Q2.3 (D)
unnamed: D5.2, J6.1, Q3.3 (D)
unnamed: D6.2, J4.2, Q5.3 (D)
unnamed: D9.2, K1.5, Q6.3 (D)
unnamed: J1.1, Q1.3
unnamed: J2.1, R8.1, R9.2
unnamed: J2.3, R6.1, R7.2
unnamed: J2.5, R4.1, R5.2
unnamed: J2.7, R2.1, R3.2
unnamed: J3.1, Q4.3 (D)
unnamed: J5.3, R18.2
unnamed: J5.4, R20.2
unnamed: J6.3, R19.2
unnamed: J6.4, R21.2
unnamed: J7.1, R23.1
unnamed: J8.1, K1.1
unnamed: J8.2, K1.3
unnamed: P1.2, U4.4
unnamed: P1.3, U4.6
unnamed: Q2.1 (G), R10.1
unnamed: Q3.1 (G), R11.1
unnamed: Q4.1 (G), R12.1
unnamed: Q5.1 (G), R15.1
unnamed: Q6.1 (G), R32.1
unnamed: R30.1, U4.3
unnamed: R30.2, U3.32
unnamed: R31.1, U4.1
unnamed: R31.2, U3.33

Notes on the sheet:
3.3V MCU power source
V12 = 12Vin/4.3
V5 = U5/2
ADC block (voltage)
Boot, reset
External 5V voltage control
External 12V voltage control
VCC BOOT0 NRST GND
5V power source
+12 GND
Cooler channels
Thermal
Alarm Buzzer

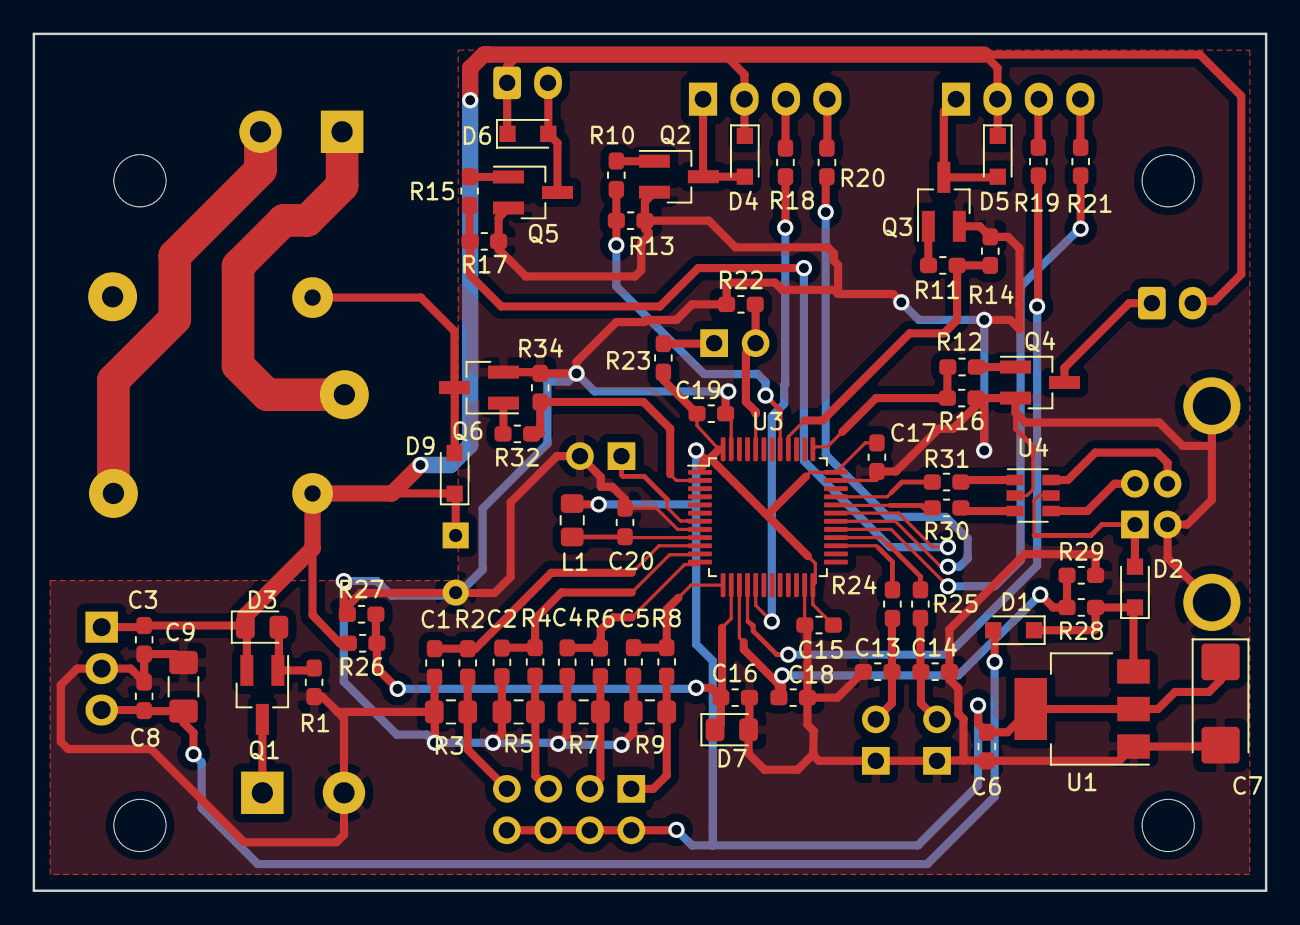
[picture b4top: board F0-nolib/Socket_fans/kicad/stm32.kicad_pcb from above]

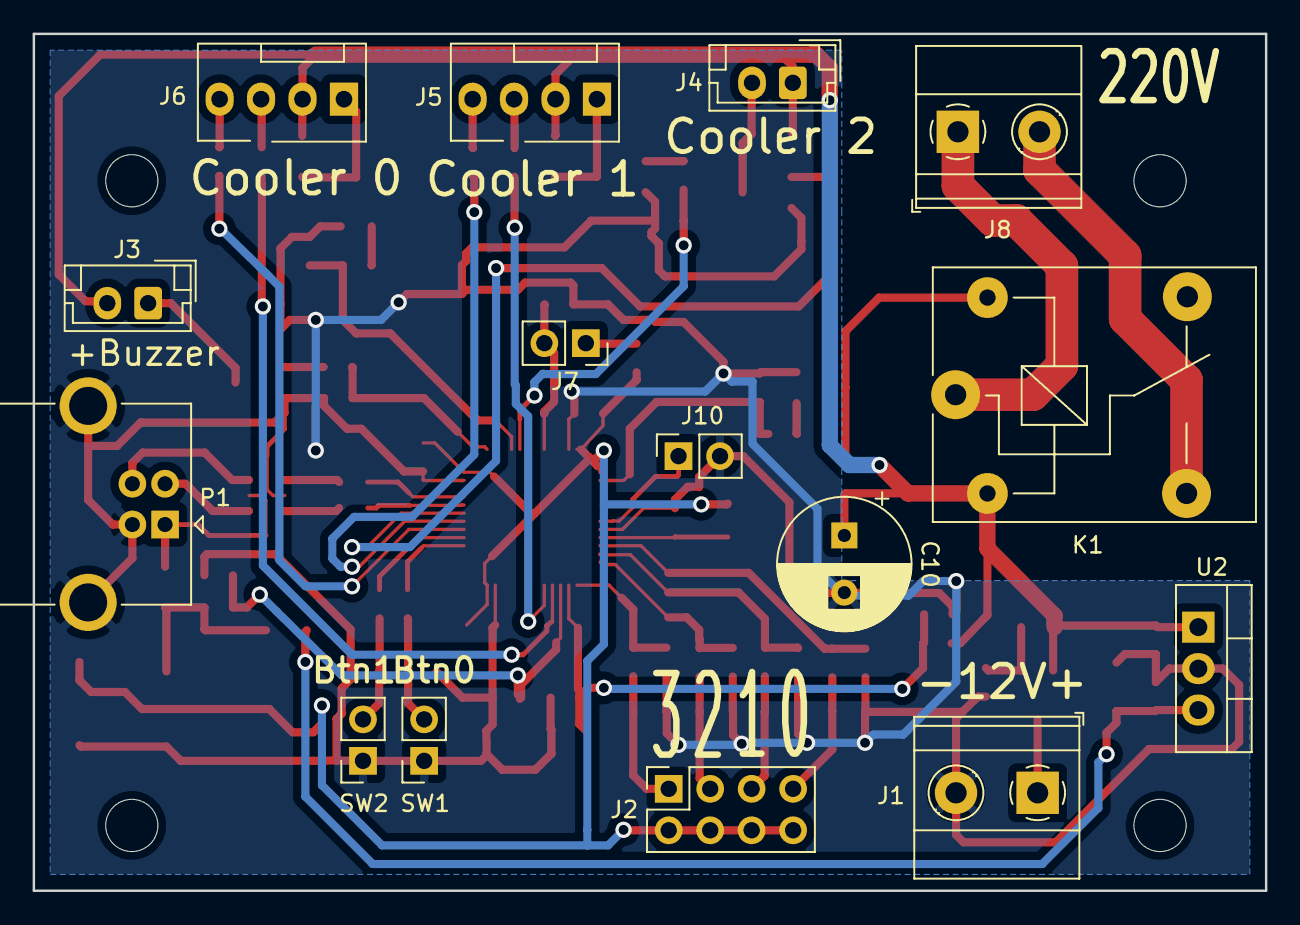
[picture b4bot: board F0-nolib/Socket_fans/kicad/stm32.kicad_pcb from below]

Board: 2 copper layers, 75.5 x 52.5 mm, 87 parts (15 on the bottom side), 57 nets.
